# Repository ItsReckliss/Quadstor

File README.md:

# Quadstor

**Quadstor** is a modular, four-lane charger for **4S Li-ion, LiPo, and LiHV packs**, designed around the simple, balance-connector-only workflow of small FPV battery chargers such as Whoopstor and Toothstor. It is currently a **hardware/firmware design project**, not a validated or production-ready charger.

This README captures the intended product, established design decisions, explored alternatives, and unresolved engineering work so contributors and coding agents can pick up the project without reconstructing earlier discussions.

> **Status (30 September 2026):** The **power-source selection board schematic is drawn** (`Hardware/Power Board/Quadstor Power Board/`, 19 parts). Its parts are synced to a 45 × 45 mm, 2-layer PCB outline, but nothing is routed yet. A netlist review found **issues to fix before layout**, listed in [§3 Power board schematic](#power-board-schematic-as-drawn-2026-09-30). The project is a git repository published at [github.com/ItsReckliss/Quadstor](https://github.com/ItsReckliss/Quadstor). A **single-lane prototype** is the next hardware milestone before tiling the design four times. **BQ25792 (charge IC) is selected for the single-lane prototype**, with the **STM32G0B1 (microcontroller)** as the MCU. The BQ25713 (original charge controller) is kept as historical context and a fallback. No schematic, tested charging system, or firmware exists yet. Dated decisions are recorded in [§12 Decision log](#12-decision-log); datasheets are in `datasheets/`.

### Key parts at a glance

Parts are referred to by part number throughout; this table gives each one's job.

| Part | Purpose | Status |
|---|---|---|
| TI **BQ25792** | Charge IC: buck-boost battery charger with integrated FETs, one per lane | Selected for prototype |
| TI **BQ25713** | Charge controller: buck-boost charger needing external MOSFETs, one per lane | Superseded; fallback |
| ST **STM32G0B1** | Microcontroller (MCU): control, cell-tap ADC, UI, USB | Selected |
| TI **TCA9548A** | I²C multiplexer: gives each lane's charge IC its own bus (fixed-address workaround) | Selected |
| TI **TPS54160A** | Buck regulator: makes the logic supply (5 V/3.3 V) from the 24–25 V input | Selected |
| SSD1306-class OLED, 0.92" | Display (prototype): header row + one lane panel | Selected (exact module TBD) |
| Toshiba **TPHR8504PL** | Power MOSFET: BQ25713 switching stage (Q1–Q4) | BQ25713 design only |
| **AONR21307** | P-MOSFET: BATFET for the BQ25713 design | BQ25713 design only |
| **AO3401A** | P-MOSFET: bleed switch for cells 2–4 (high-side, cell-referenced) | Proposed (owner suggestion); datasheet in repo |
| **AO3400A** | N-MOSFET: bleed switch for cell 1 (ground-referenced) | Proposed |
| **2N7002** | Small N-MOSFET: level-shifting gate driver for each AO3401A | Proposed |
| BZT52C5V1 (5.1 V Zener) | Gate-source clamp protecting each AO3401A's ±12 V gate rating | Proposed |
| **NCE6003X** / **NTD5865NLT4G** | N-MOSFET: earlier bleed-switch candidates | Superseded by AO3401A/AO3400A proposal |
| TLV755P / AP2112K | LDO regulator: 5 V → clean 3.3 V | Proposed |
| 0603 10 kΩ NTC (B ≈ 3380–3435 K) | Temperature sensor on the charge IC's TS pin, next to the JST-XH | Decided (exact part TBD) |
| USBLC6-2SC6 | USB ESD protection on D+/D− | Proposed |
| TI **CD74HC4067SM96** | 16:1 analog multiplexer (SSOP-24, tape and reel): routes the 16 divided tap voltages to one MCU ADC pin | Selected (datasheet not yet in `datasheets/`) |
| **TLV9001** / **MCP6001** | Op-amp: unity-gain buffer between the analog mux and the ADC | Proposed |
| Tag-Connect TC2030 | Connector-less SWD programming/debug footprint | Proposed |
| Mean Well 24 V / 200 W | Internal power supply (model TBD) | Planned |
| **AOD409** (×3) | P-MOSFET, TO-252: power-board source switches (Q1 PSU path; Q2/Q3 back-to-back on the 6S path) | In power-board schematic |
| **2SA1213-Y** | PNP transistor, SC-62: power board, pulls the 6S FET gates off when the PSU is present (Q4) | In power-board schematic |
| **AO3400A** (power board) | N-MOSFET: power board PSU-present detector that drives Q4 (Q5) | In power-board schematic |
| **BZT52C12V** | 12 V Zener: power board gate-source clamp for the 6S FETs (U1) | In power-board schematic |
| **SMCJ30A-TR** (×2) | TVS diode, 30 V standoff: power board surge clamp on each input (D1 PSU, D2 6S) | In power-board schematic |
| Littelfuse **01550900M** (×2) | SMD fuse: power board, one per input (FH1 PSU, FH2 6S) | In power-board schematic; rating to confirm |

## 1. Product goals

- **Four independent 4S charging lanes**, each with a 5-pin JST-XH balance connector. Packs can be inserted/removed independently without disturbing other lanes.
- **Balance-connector-only charging:** the outer connector pins carry pack charging current; intermediate pins provide cell taps. No separate XT30/XT60 lead is required for the battery being charged.
- **User-selectable charging current:** 0.1–2.0 A per lane in 0.1 A steps. Earlier discussions refer both to a global current setting and per-lane adjustment; the UI behavior should be finalized in firmware requirements. The electrical architecture must support independently controlled lanes.
- **Global per-cell target voltage presets:** 3.80 V, 3.85 V, 4.20 V, and 4.35 V, corresponding to 15.20 V, 15.40 V, 16.80 V, and 17.40 V for a 4S pack. The 4.35 V setting is **LiHV only** and must not be applied to conventional 4.20 V/cell packs.
- **Passive cell balancing**, individual cell-voltage measurement, pack monitoring, and safe fault handling on every lane.
- Compact **OLED, two-button, and beeper** interface. The UI uses a **single OLED**. The prototype uses a small 0.92" OLED showing a **header** (input voltage, target voltage, set current) and **one lane panel**. The final version uses a larger single OLED with that lane panel **tiled four times** and a reorganized header (see §7).
- Operate from an **internal 24 V / 200 W Mean Well PSU** or an external **6S battery via XT60**, automatically preferring the PSU when available.
- Modular design: develop, assemble, and characterize one complete lane, then replicate it four times.

## 2. System overview

```text
                     Internal 24 V / 200 W PSU
                                |
External 6S pack -> XT60 -> input protection / source selection
                                |
                   Protected, selected VIN bus
                                |
                   Bulk decoupling near lanes
                                |
            +-------------------+-------------------+
            |                   |                   |
       Charger lane 1      Charger lane 2      ... lane 4
       4S JST-XH           4S JST-XH              4S JST-XH
       Cell taps           Cell taps              Cell taps
       4 bleed paths       4 bleed paths          4 bleed paths
            |                   |                   |
       I2C mux ch0         I2C mux ch1            I2C mux ch3
            +-------------------+-------------------+
                                |
                      TCA9548A I2C mux
                                |
        STM32G0B1: ADC (cell taps, VSENSE) / GPIO / USB
                                |
   Single OLED (header + lane panels) / 2 buttons / buzzer / LEDs / USB-C / SWD

Logic power: selected VIN -> TPS54160A buck -> 3.3 V (optionally 5 V -> LDO -> 3.3 V)
```

Each lane has its own charger power stage, pack sensing, balancing, and charging state. The **tiled hardware lane unit** is: BQ25792 charge IC + its inductor/capacitors, JST-XH, cell-tap sensing, four bleed paths, and NTC. The MCU, regulators, I²C mux, the single OLED, buttons, buzzer, USB-C, and SWD are **shared and are not tiled**. Tiling of the UI happens in **firmware**: one lane panel drawn four times on the one display (§7).

The BQ25792 charge IC has a fixed 7-bit I²C address (**0x6B**), so four of them cannot share one bus. A **TI TCA9548A** (8-channel I²C switch/multiplexer) gives each lane's charge IC its own downstream channel. The proposed channel map is ch0–ch3 for lanes 1–4 and ch4–ch7 spare. The single OLED (SSD1306-class, typically 0x3C) sits on the upstream bus, or on a spare channel if needed. If the final larger display uses SPI, it connects directly to the MCU instead. Tie A0–A2 low (address 0x70), connect RESET to an MCU GPIO to clear stuck buses, and fit pull-ups on the upstream bus and on each used downstream channel. The TCA9548A runs from 1.65–5.5 V at up to 400 kHz. This channel map is **proposed** until it is drawn in a schematic.

## 3. Power input and source selection

### Intended inputs

| Input | Nominal | Relevant range / notes |
|---|---:|---|
| Internal Mean Well PSU | 24 V, 200 W | Default source when present. Exact PSU model not yet recorded here. |
| External field battery | 6S Li-ion/LiPo via XT60 | Up to **25.2 V** for standard 4.20 V/cell 6S. Verify any LiHV input separately. |

The separately developed **power-selection board** accepts `VBAT`, `GND`, `GND`, and `VPSU`, and provides `VOUT`, `GND`, and `VSENSE`. `VSENSE` is intended to feed an MCU ADC through a resistor divider. The selected output feeds the charger board directly, with additional local bulk and high-frequency bypass capacitors at each charger IC.

**Confirmed by the owner (2026-09-29):** the existing power board already **handles source selection**, **electrically disconnects the XT60 input when the PSU is on**, and **blocks backfeed**. The charger lanes therefore do not need their own source selection or reverse-current blocking. ~~**Open item:** confirm whether the power board has a **TVS and/or soft-start**~~ **Answered by the schematic (2026-09-30):** both inputs have an SMCJ30A TVS diode, but it clamps far above the BQ25792 charge IC's 30 V absolute maximum, and there is no dedicated soft-start. See the review below. **Review note:** the drawn schematic does **not** block backfeed into the PSU (finding 2 below), so the owner's earlier confirmation needs to be rechecked.

Discussed input protection/components:

- 15 A fuse on the power input path (final placement/rating must be verified).
- Input TVS diode; proposed 100 µF bulk capacitor and 1 µF bypass capacitor.
- Back-to-back P-channel MOSFETs on the XT60 path for source isolation/reverse-current blocking.
- PSU-priority behavior: when PSU is present, block the external battery from supplying the bus; use the external battery when PSU is absent.
- `VSENSE` divider for firmware supply-voltage monitoring. Confirm which node it measures in the current schematic.

### Power board schematic (as drawn, 2026-09-30)

The KiCad 10 project is `Hardware/Power Board/Quadstor Power Board/`. Its parts were imported from LCSC with the EasyEDA importer into the project-local `EasyEDA.kicad_sym` / `EasyEDA.pretty` libraries. All 19 footprints are on a **45 × 45 mm, 2-layer** board outline (imported from DXF), with no tracks or copper zones yet.

| Ref | Part (LCSC) | Function |
|---|---|---|
| FH1, FH2 | Littelfuse 01550900M SMD fuse (C108518) | Input fuses: FH1 on `VPSU`, FH2 on `VBAT` (6S/XT60). Current rating not yet recorded. |
| D1, D2 | SMCJ30A-TR TVS diode (C1975473) | Surge clamps: D1 on `VPSU_Protected`, D2 on the fused 6S node |
| C1, C2 | 1 µF 100 V X7R 1206 (C91151) | C1 on `VPSU_Protected`, C2 on `VOUT` |
| Q1 | AOD409 P-MOSFET (C36220) | PSU path switch: source `VPSU_Protected`, drain `VOUT`. Gate is biased by the R1/R2 divider to Vgs ≈ −VPSU/2. |
| Q2, Q3 | AOD409 P-MOSFET (C36220) | 6S path, back-to-back with common sources. Q2 drain on the fused battery, Q3 drain on `VOUT`. |
| U1 | BZT52C12V 12 V Zener (C5182293) | Clamps the 6S FETs' gate (`VBAT_Gate`) to 12 V below their common source |
| Q4 | 2SA1213-Y PNP transistor (C396014) | When on, shorts `VBAT_Gate` to the common source, turning the 6S path off |
| Q5 | AO3400A N-MOSFET (C20917) | PSU-present detector: gate from the R6/R7 divider on `VPSU_Protected`; pulls Q4's base low through R4 |
| R1–R7 | Labeled "220k"; library part is RC0402FR-071KL (C106235) | Gate/bias dividers and pull-downs (see finding 3) |

**Intended operation:** with the PSU present, Q1 conducts and Q5 turns Q4 on, which holds the 6S FETs off, so the PSU has priority. With the PSU absent, Q5 and Q4 are off, and R3 pulls `VBAT_Gate` low (clamped by U1), turning Q2/Q3 on. Back-to-back Q2/Q3 block current in both directions when off.

Not yet in the schematic: input/output **connectors** (XT60, PSU input, output to the charger board; the nets are global labels only), the `VSENSE` divider, and the duplicate GND pins of the board interface.

**Review findings (Claude, from a netlist exported with kicad-cli on 2026-09-30; verify before layout):**

1. **Q2's gate is unconnected** (ERC net `unconnected-(Q2-G-Pad1)`). A third `VBAT_Gate` label exists but isn't attached. Without the gate, Q2 conducts only through its body diode or turns on unpredictably, and the 6S path can't block reverse current. Connect Q2's gate to `VBAT_Gate`.
2. **Q1 doesn't block backfeed into the PSU, and the PSU-detect can be fooled.** Q1's body diode conducts from drain to source (`VOUT` → `VPSU_Protected`). When running from the 6S pack with the PSU off, the pack feeds the PSU output through that diode. That also lifts `VPSU_Protected` to about VOUT − 0.7 V, which turns Q5 → Q4 on and shuts the 6S path off. The likely result is the battery path oscillating or failing to stay on. Fixing this needs a PSU-side switch that blocks in both directions (for example a back-to-back pair or an ideal-diode controller), or a PSU-present signal taken upstream of anything `VOUT` can back-drive.
3. **The resistor value doesn't match the part.** All seven resistors say **220k**, but their library part and LCSC number are **RC0402FR-071KL, which is 1 kΩ**. A BOM ordered by LCSC number would fit 1 kΩ. R1/R2 would then draw ~12 mA from 24 V and dissipate ~0.14 W each, above a 0402's typical 1/16 W rating. Pick a real 220 kΩ 0402 part and LCSC number.
4. **The TVS doesn't protect the BQ25792 charge IC's 30 V absolute maximum.** The SMCJ30A has a 30 V standoff, 33.3 V minimum breakdown, and ~48 V clamping at rated current (typical datasheet values). It catches large surges but lets `VOUT` exceed 30 V during a spike. This matches the reasoning behind "no per-lane TVS" in §4. Hot-plug ringing still needs scoping, and possibly a lower-voltage clamp or a soft-start/inrush limiter.
5. **Q5's gate margin is thin.** The R6/R7 divider gives VGS = VPSU/2, which is 12 V at 24 V. The AO3400A's gate rating is ±12 V (verify; datasheet not in repo), so a Mean Well PSU trimmed up, or a spike, overstresses it. Use a lower divider ratio (for example 220k over 100k) or a Zener clamp.

**Important:** Do not assume the power board provides a regulated 24 V output. The charger must tolerate the actual selected input voltage and transients. Absolute maximum is **not** a recommended continuous design target. Check the chosen IC's recommended operating range, transient headroom, TVS coordination, and hot-plug behavior before powering a prototype.

**BQ25792 (charge IC) input-voltage findings (datasheet SLUSDG1C, checked 2026-09-29):**

| Parameter | Value | Implication |
|---|---|---|
| VBUS/VAC absolute maximum | 30 V | A 25.2 V 6S pack will not damage the IC in steady state. Hot-plug ringing must stay below 30 V. That is the power board's job (TVS/soft-start still to be confirmed), because a per-lane TVS cannot do it (see §4). |
| VBUS recommended operating range | 3.6–24 V | The 24 V PSU is at the limit and acceptable. A full 6S pack (25.2 V) is ~1.2 V above the recommended range. |
| VAC OVP, highest setting (`VAC_OVP[1:0]=00`, default) | Rising: 25.2 / 26.0 / 26.8 V (min/typ/max). Falling: 24.4 / 25.2 / 26.0 V | A low-tolerance part could trip OVP on a fully charged 6S pack and stay off until the input falls below ~24.4 V. The expected result is a lane refusing to start or dropping out, not damage. |

**Decision (2026-09-29):** accept 6S direct input for the prototype and characterize it. Test with a freshly charged 6S pack, and scope VBUS during XT60 hot-plug. Firmware should detect and report the VAC OVP fault and retry. If lanes trip in practice, the options are a ~1 V drop on the 6S path (a diode, or preferably an ideal-diode controller for lower loss), a pre-regulator, or limiting the field input to 5S (21 V).

The proposed 200 W PSU is nominally sufficient for the planned four-lane output power under ideal conditions (4 × 17.4 V × 2 A = **139.2 W** at the maximum LiHV target), but input power, losses, balancing dissipation, wiring limits, and thermal derating must be measured.

## 4. Charger lane: baseline and alternative

### Original baseline: TI BQ25713 (charge controller)

The original architecture uses **one BQ25713 buck-boost charger IC per lane**, with an external switching power stage, an external BATFET, and MCU-controlled passive balancing. This is the historical baseline, not proof that the current schematic still uses it.

| Function | Discussed component | Quantity per lane | Status |
|---|---|---:|---|
| Buck-boost charger controller | TI **BQ25713** | 1 | Original baseline |
| Main switching MOSFETs Q1–Q4 | Toshiba **TPHR8504PL** N-MOSFET | 4 | Selected for original design |
| BATFET | **AONR21307** P-MOSFET | 1 | Selected/proposed; validate exact suffix and pinout |
| Passive balancing switches | **NCE6003X** N-MOSFET | 4 | Proposed; other candidates considered |
| Balance bleed resistors | **110 Ω, 1210, 0.5 W** | 4 | Proposed; requires thermal validation |
| Battery connector | **5-pin JST-XH** | 1 | Required interface |
| Cell sensing | MCU ADC with suitable front-end | 4 cell voltages derived from taps | Architecture only; protection/circuit not finalized |

The uploaded TPHR8504PL (power MOSFET) datasheet specifies a **40 V** drain-source rating and typical `RDS(on)` of **0.7 mΩ at VGS = 10 V** (0.85 mΩ max under its stated test conditions). It has substantial gate charge (103 nC typical at 10 V in the datasheet's stated test setup). Validate compatibility with the selected charger gate drivers, switching frequency, layout, and thermal design; low on-resistance alone does not establish suitability. The exact package variant/footprint must match the ordered device.

The **NTD5865NLT4G** was also investigated as a possible balancing MOSFET; it is **not** established as the final selection.

### Prototype selection: TI BQ25792 (charge IC)

**Decision (2026-09-29):** the single-lane prototype uses the **BQ25792**, a buck-boost charger with **integrated switching FETs** (datasheet in `datasheets/BQ25792_datasheet.pdf`, rev SLUSDG1C). It replaces the BQ25713's external Q1–Q4 stage, so the TPHR8504PL switches and the AONR21307 BATFET in the table above do **not** apply to this design. Never mix the two architectures' BOMs.

Datasheet facts relevant to Quadstor:

| Item | Datasheet value | Notes |
|---|---|---|
| Charge voltage (VREG) | 3.0–18.8 V, 10 mV steps | Covers all presets, including 17.40 V LiHV. |
| Charge voltage accuracy | +0.65% / −0.85% | At 17.40 V, +0.65% is +113 mV (≈4.378 V/cell average). Firmware must use per-cell measurements, not rely on VREG alone, to keep LiHV cells ≤4.35 V. |
| Charge current (ICHG) | 50 mA–5 A, 10 mA steps | Covers 0.1–2.0 A. Low-current accuracy is worse; for example, ±7.5% at 0.5 A. |
| Input current limit (IINDPM) | 0.1–3.3 A | Also limited by the ILIM_HIZ pin divider (V = 1 V + 0.8 × IINDPM). |
| Input voltage | See §3 | 24 V recommended max, 30 V abs max. |
| I²C | Fixed 7-bit address 0x6B | Requires the TCA9548A mux (§2). |
| Built-in ADC | VBUS, IBUS, VBAT, IBAT, TS, die temperature, and more | Lets the MCU read pack voltage/current and NTC temperature through I²C, which saves MCU ADC channels. |
| REGN | ~5 V LDO, 30 mA limit, needs 4.7 µF | For the IC's gate drive and TS bias only. **Do not** power the MCU/logic from it. |

Per-lane pin handling (proposed; verify against the datasheet when drawing the schematic):

- **PROG:** 17.4 kΩ selects 4S at 1.5 MHz (use a ~1 µH inductor); 27.0 kΩ selects 4S at 750 kHz (use a ~2.2 µH inductor). Choose based on efficiency and thermal testing.
- **VAC1/VAC2:** connect to VBUS, and tie **ACDRV1/ACDRV2** to GND. The power board does source selection, so the BQ25792's dual-input FETs are not fitted.
- **SDRV:** tie to GND or BAT because no ship FET is used.
- **CE (active low):** drive from an MCU GPIO with a **pull-up**, so charging is disabled while the MCU is in reset. It must never float.
- **INT and STAT:** open-drain outputs; use 10 kΩ pull-ups to 3.3 V and route to the MCU. INT is needed for fault handling. STAT is optional.
- **TS / temperature sensing (decided 2026-09-29):**
  - Fit **5.23 kΩ from REGN to TS** and **30.1 kΩ from TS to GND**, the TI typical-application divider in nearest E96 values. This gives the default window: charging suspends at ~0 °C and ~60 °C, with JEITA reductions near the edges.
  - Fit a **0603 10 kΩ NTC from TS to GND**. Use B ≈ 3380–3435 K; the datasheet recommends the 103AT-2 at B = 3435. 5% tolerance is acceptable.
  - Place the NTC **right next to the JST-XH connector**. It measures connector/board temperature, **not** the pack.
  - TS must **never float**. If temperature sensing is ever dropped, replace the NTC with a fixed 10 kΩ resistor.
- **D+/D−:** USB adapter detection is not used; follow the datasheet for unused handling.
- **OTG (reverse boost) mode (decided 2026-09-29):** the BQ25792 charge IC can boost the battery back out to VBUS. Firmware must **never enable OTG**, and must **read back that OTG is disabled** after configuring the IC, so a pack can never drive the input bus.
- **SYS:** the BQ25792 is a power-path (NVDC) charger, so SYS is powered from the pack when the input is removed. Fit only the required capacitors on SYS, with no other loads.
- **Input protection per lane (decided 2026-09-29):**
  - **No per-lane TVS.** The standoff would have to exceed 25.2 V (full 6S), and such a TVS clamps around 40 V, which is above the 30 V absolute maximum. Surge protection belongs on the power board (§3).
  - Add a **do-not-populate (DNP) footprint** for the datasheet's **input RC snubber (~2 Ω + 2.2 µF) on VBUS**. Fit it only if ringing shows up on the bench.
  - **Input capacitors:** VBUS gets 1× 0.1 µF + 2× 10 µF; PMID gets 1× 0.1 µF + 3× 10 µF. All are **50 V X7R**, derated for the 25.2 V input because ceramics lose capacitance under DC bias.
- **Other passives (datasheet values; ratings proposed):** SYS 1× 0.1 µF + 5× 10 µF (≥25 V, 35 V preferred at 17.4 V); BAT 2× 10 µF (≥25 V); BTST1 and BTST2 47 nF each; REGN 4.7 µF (10 V).

The BQ25713 charge-controller design remains a fallback if the BQ25792 charge IC fails characterization (input range, thermals, or accuracy). Switching back requires redesigning the power stage, not a part swap.

## 5. Battery connector and cell measurement

Each output is a **five-pin JST-XH connector for one 4S pack**. Number the contacts by **electrical function**, not assumed footprint orientation:

| Electrical node | Function |
|---|---|
| `B-` | Pack negative; charger negative connection |
| `B1` | Junction between cells 1 and 2 |
| `B2` | Junction between cells 2 and 3 |
| `B3` | Junction between cells 3 and 4 |
| `B+` | Pack positive; charger positive connection |

With taps referenced to `B-`, compute cell voltages as `Vcell1 = VB1`, `Vcell2 = VB2 - VB1`, `Vcell3 = VB3 - VB2`, and `Vcell4 = VB+ - VB3`.

**The MCU cannot directly connect upper-cell taps to ordinary 3.3 V ADC pins.** Provide properly rated dividers/buffers or a suitable multi-cell monitor, input protection, filtering, accurate reference/calibration, and safe handling of missing/intermittent contacts. Check voltage differences and resistor tolerances at every tap. Keep measurement input current and connector contact resistance in mind when charging through the same plug.

**Measurement architecture (decided 2026-09-29): an analog multiplexer feeding one MCU ADC pin.** The ADC is ground-referenced, so the system measures **tap voltages**, not cells directly. Per lane, the four taps B1, B2, B3, and B+ are measured, and cell voltages are computed by subtraction as above. Four lanes × 4 taps = **16 channels, one 16:1 analog mux**, with 4 MCU select GPIOs and 1 ADC input. `VSENSE` keeps its own ADC pin.

- **Pack voltage:** the B+ tap *is* the pack voltage, so no extra channel is needed. The BQ25792 charge IC also reports VBAT over I²C, which serves as an **independent cross-check**. A mismatch between the two ADCs should raise a fault.
- **Signal chain, per tap:** divider (0.1%) → series resistor + clamp → mux input. After the mux: a **unity-gain op-amp buffer** → MCU ADC.
  - Divide **before** the mux, because common muxes only pass signals within their 3.3–5 V supply.
  - The buffer isolates the divider's high source impedance and the mux on-resistance from the ADC sampling capacitor.
- **Settling:** allow settling time after each channel switch (tens of µs; confirm on the bench). Pause balancing on a lane while reading its taps.
- **Unpowered safety:** a pack can be connected while the board is unpowered, so the series resistors must limit injection current into the unpowered mux.
- **Standby drain:** the dividers drain packs left connected (e.g. ~170 µA at 100 kΩ total). Use high-value dividers (then the buffer is mandatory) or switch the dividers off when idle.
- **Accuracy:** all taps share one mux, buffer, and ADC path, so the offset is common. Differencing still amplifies divider error: 0.1% at ~13–17 V is roughly ±13–17 mV per tap. Plan two-point calibration per channel.
- **Candidate parts (proposed):**
  - **Selected (2026-09-29): TI CD74HC4067SM96** (16:1 analog multiplexer, SSOP-24, 0.65 mm pitch; the SOIC-24 variant CD74HC4067M96 is electrically identical).
    - Power it from 3.3 V (same as the ADC). Signals must stay within GND to VCC.
    - Tie E (active-low enable) to GND or to a GPIO.
    - On-resistance is ~70 Ω typical at 4.5 V and higher at 3.3 V. The buffer makes this irrelevant.
    - **Off-leakage × divider Thevenin resistance is an error source:** e.g. 1 µA × 25 kΩ = 25 mV at the ADC, ≈175 mV referred to a 17 V tap. Check the datasheet's leakage over temperature when choosing divider values.
  - Alternative: **ADG706** (Analog Devices, 16:1 analog multiplexer, ~2.5 Ω, lower leakage).
  - **TLV9001** or **MCP6001** (rail-to-rail op-amp) as the buffer.
- **Single-lane prototype:** fit the full 16:1 mux even though only 4 channels are used, to validate the four-lane measurement chain.

Tap front-end details still to design: divider values scaled to the ADC reference (for example B+ at 17.4 V max scaled to ≤2.5 V), clamp type, filter capacitor, and open/missing-tap detection (such as a weak bias that drives an unconnected tap to an implausible reading). A dedicated multi-cell monitor IC per lane remains an alternative if accuracy proves insufficient.

## 6. Passive balancing

The proposed architecture has **four independent bleed paths per lane**, one across each cell, each controlled by an external MOSFET under MCU supervision. The original candidate network is **110 Ω / 0.5 W (1210)** per cell, switched using NCE6003X MOSFETs (or a validated equivalent).

Approximate ideal resistor dissipation and bleed current:

| Cell voltage | Current through 110 Ω | Resistor dissipation |
|---:|---:|---:|
| 3.80 V | 34.5 mA | 0.131 W |
| 4.20 V | 38.2 mA | 0.160 W |
| 4.35 V | 39.5 mA | 0.172 W |

These values are estimates before switch losses and component tolerances. Verify each bleed path's **gate-drive voltage relative to its cell**, especially upper cells; do not connect high-side cell-referenced gates directly to ground-referenced MCU GPIOs. Upper-cell switches sit up to ~13 V above ground, so they need level shifting.

**Proposed bleed-switch circuit (2026-09-29).** The owner suggested the AO3401A (P-MOSFET). Its figures below were checked against `datasheets/AO3401A.pdf` (AOS Rev 3.1, Dec 2023) on 2026-09-30.

- **Cells 2–4 (upper cells):**
  - The **AO3401A** source goes to the cell's top node (B1/B2/B3/B+), and its drain goes through the 110 Ω bleed resistor to the cell's bottom node.
  - A 100 kΩ gate-to-source pull-up holds it off.
  - A **2N7002** N-MOSFET, gate driven by an MCU GPIO with a 100 kΩ pull-down, pulls the gate toward GND through ~47 kΩ.
  - A **5.1 V Zener** from gate to source clamps V_GS to about −5 V.
  - Why this is needed: the AO3401A's V_GS limit is **±12 V**, so the gate must never be pulled straight to GND. On the top cell that would apply ~−17 V.
  - AO3401A (datasheet): −30 V V_DS, ±12 V V_GS, 47 mΩ typical / 60 mΩ max at V_GS = −4.5 V, V_GS(th) −0.5 / −0.9 / −1.3 V (min/typ/max), SOT-23. At 40 mA the conduction loss is negligible.
  - Off-state leakage I_DSS is at most 1 µA at 25 °C (5 µA at 55 °C) per switch. This is small next to the tap-divider drain (§5) but adds to it on a stored, plugged-in pack.
- **Cell 1 (bottom cell):** B− is GND, so an **AO3400A** N-MOSFET is driven directly from a GPIO, with a 100 kΩ pull-down.
- **Why not N-channel on the upper cells:**
  - An upper-cell N-FET's source sits at that cell's bottom node (up to ~13 V). Its gate would need to be driven to about the cell's top node, which requires a high-side (P-type) switch plus its own driver. That is two driver transistors per upper cell.
  - A P-FET with its source on the cell's top node turns on by pulling its gate *down*, which one ground-referenced 2N7002 can do.
  - Totals per lane: 7 transistors with the proposed P-channel scheme, versus 10 for all N-channel.
- **Alternative:** one PhotoMOS solid-state relay per cell (for example the Panasonic AQY21x class). It needs no level shifting and fails off, but costs more (~$1–2 each) and is larger.
- **Fail-safe:** with the GPIO low, floating, or in reset, every bleed switch is off.
- **Per lane:** 3× AO3401A, 1× AO3400A, 3× 2N7002, 3× 5.1 V Zener.
- **To validate:** off-state leakage (a continuous drain on a stored, plugged-in pack), and tap-reading error while bleeding. Firmware should pause bleeding during cell measurements.

Four lanes × 4 bleed paths = **16 MCU GPIOs**, and every gate must have a pull-down or equivalent so all bleeders are **off during reset**. Ensure balancing cannot remain latched on after MCU reset and that balancing and charging decisions account for measured cell voltages, thermal limits, and the relatively low ~40 mA bleed rate compared with up to 2 A charging current.

## 7. MCU, firmware, and controls

### MCU: STM32G0B1 (microcontroller)

**Decision (2026-09-29):** STM32G0B1 (Cortex-M0+, 64 MHz; datasheet in `datasheets/STM32G0B1_datasheet.pdf`). It was chosen for its 16-channel 12-bit ADC, crystal-less USB 2.0 FS device, and ROM bootloader.

- **Package (proposed): LQFP64 (STM32G0B1RET6).** With the analog mux, the four-lane pin budget is 1 ADC for taps + 4 mux selects + 1 ADC for `VSENSE`, 16 balance GPIOs, 4 × CE + 4 × INT (optionally 4 × STAT), I²C, TCA9548A (I²C mux) RESET, USB D+/D−, SWD, 2 buttons, buzzer PWM, status LEDs, and possibly SPI for the final display. That is too tight for a 48-pin package. Use the same part on the single-lane prototype so firmware carries over.
- **Support circuitry:** 100 nF at every VDD pin plus 4.7 µF bulk; VDDA filtered with a ferrite bead, 1 µF, and 100 nF; 100 nF on NRST. Use VREF+ with the internal VREFBUF (2.048/2.5 V) or an external reference for ADC accuracy. No HSE crystal is needed, because USB uses HSI48 with clock recovery.
- **Safe defaults:** all charge-enable and balance outputs must default to off through external pulls, independent of firmware (see §6 and §8).

### Logic power

**Decision (2026-09-29):** a **TI TPS54160A** (3.5–60 V in, 1.5 A, non-synchronous buck; datasheet in `datasheets/tps54160a.pdf`) generates the logic supply from the selected VIN. An LDO from ~25 V was rejected because it would dissipate ~1 W at only 50 mA.

Design notes:

- **Switching frequency:** the minimum on-time is 130 ns typical. For 3.3 V output from up to 30 V in, f_SW(max) ≈ (3.3 + 0.5) / (30 V × 130 ns) ≈ 950 kHz. Use **~500–700 kHz**.
- **Catch diode:** requires an external Schottky from PH to GND, rated ~60 V / 1 A.
- **EN UVLO:** use a divider on EN so the regulator does not start until the input reaches roughly 8 V or more.
- **Components:** use 50 V-rated input capacitors, and compute compensation and the inductor with TI WEBBENCH.
- **Load:** the logic load is expected to be ≤ ~150 mA (MCU, OLEDs, mux, sensing), far below the 1.5 A rating.
- **Proposed topology:** buck to **5 V**, then a small low-noise LDO regulator (for example TLV755P or AP2112K) to 3.3 V. This gives a quieter ADC supply, a 5 V rail for the buzzer, and allows USB VBUS to be diode-ORed into the 5 V rail (see below). Buck directly to 3.3 V is acceptable if that is not wanted.

### Programming, USB, and diagnostics

**Decision (2026-09-29):** a **USB-C port on the controller/lane board** is for **flashing (USB DFU) and diagnostics (USB CDC virtual COM port)**. It is **not** a charging power input, since USB cannot supply the charging power, and it does not belong on the power board.

- **USB-C device wiring:** 5.1 kΩ Rd from each CC pin to GND; USB ESD protection (for example USBLC6-2SC6) on D+/D−; D+/D− to PA12/PA11.
- **Optional:** USB VBUS → Schottky → 5 V logic rail. This lets the MCU, OLEDs, buttons, buzzer, and USB be brought up with only a USB cable while the chargers stay unpowered, because their VBUS comes only from the power board. Ensure VBUS is never back-fed.
- **DFU entry:** a blank device boots the ROM bootloader automatically. Once flash is programmed, DFU entry needs either a firmware "jump to bootloader" command or the BOOT0 pin. On STM32G0 the BOOT0 function shares PA14 with SWCLK and is governed by option bytes (`nBOOT_SEL`/`nBOOT0`). Verify in RM0444 and AN2606 before relying on a BOOT button.
- **Buttons:** a **RESET button** (NRST to GND) and a **BOOT button** (PA14 to 3.3 V with a 10 kΩ pull-down) are planned for the prototype.
- **SWD is kept.** It is needed for debugging (breakpoints) and for recovery when bad firmware breaks USB. Earlier plans called for a JST-XH SWD header; the updated plan is a **Tag-Connect TC2030 footprint or bare pads** (3V3, SWDIO, SWCLK, NRST, GND) on both prototype and production, with no connector BOM cost. An optional UART TX test pad is useful for early logging.

### Intended UI

**Decision (2026-09-29):** the UI parts (OLED, buttons, buzzer, status LEDs) go on the single-lane prototype board so they can be verified before the four-lane build.

- **Single OLED (decided 2026-09-29):** there is exactly **one** display, never one per lane.
  - **Prototype:** a small **0.92" OLED**. Most modules this size are 128×32 SSD1306 I²C (display controller); confirm the actual resolution and controller of the purchased module. Connect it with a 4-pin header (VCC, GND, SCL, SDA) rather than a bare glass panel with FPC and charge-pump capacitors.
  - **Final:** a **larger single OLED** (part TBD). The prototype's lane panel is **tiled four times** on it, and the header is added or reorganized to fit.
- **Header row:** shows **input voltage, target voltage, and set current**, and may also show the power source and mute state if space allows. For example, `24.1V 4.20V 2.0A` is 16 characters, about 96 px in a 6 px-wide font, so it fits in 128 px.
- **Lane panel (the tiled unit in firmware):** connection/charging state, pack and cell voltages, charge current, and fault or completion. Implement it as a **self-contained, fixed-size render component** that takes a lane index and an (x, y) origin, so the final display simply draws it four times.
- **Proposed layout (not decided):**
  - On a 128×32 prototype display, use an **8 px header row + a 128×24 lane panel**.
  - A final **256×64** display (for example the SSD1322 class, commonly 2.8"–3.12") would fit the 8 px header plus four 128×24 panels in a 2×2 grid (8 + 48 = 56 px ≤ 64 px) without redesigning the panel.
  - Larger 256×64 panels are often SPI and 4-bit grayscale, which needs a different driver than the SSD1306. Keep SPI-capable MCU pins available.
- **Refresh budget:** a full 128×32 SSD1306 frame is 512 bytes, ~13 ms at 400 kHz I²C. A 256×64 grayscale frame is 8 KB, which is why the final display should use SPI and/or partial updates.
- **Two physical buttons:** tactile switches to GND with pull-ups and an optional 100 nF debounce, on interrupt-capable pins. One combines **Start/Stop + Current** and the other **Mute + Voltage**, using click/hold interactions. Final click/hold mappings, per-lane selection, and display layout need a firmware specification.
- **Beeper:** a passive magnetic buzzer driven from a timer PWM output (allowing distinct tones) through an N-MOSFET/NPN from the 5 V rail, with a flyback diode. It gives status, completion, and error notifications with mute support.
- **Status LEDs:** one power LED on 3.3 V plus one or two GPIO LEDs (~1 kΩ) for heartbeat and fault, useful before the OLED works.

The recorded product goals include a global current setting **and** a requirement to independently adjust each lane's current; this needs a deliberate UI decision rather than an assumed implementation. The planned header display shows one "set current," which implies a **global setpoint by default**. Whether per-lane overrides exist, and how they are shown in the lane panels, is still open. At minimum, the charger hardware and firmware should independently control and stop each lane.

### Suggested firmware modules (proposed, not existing code)

```text
firmware/
  board/             # GPIO, ADC, I2C, timer, and peripheral definitions
  power/             # VIN measurement and source status
  charger/           # Charger-IC abstraction, one instance per lane
  sensing/           # Tap acquisition, calibration, cell-voltage calculation
  balancing/         # Per-cell bleed control and safeguards
  safety/            # Fault detection, limits, watchdog, safe shutdown
  ui/                # OLED pages, button events, buzzer
  app/               # Global settings and four independent lane state machines
```

A sensible lane state machine to implement and validate is `DISCONNECTED -> DETECTED -> VALIDATING -> CHARGING -> COMPLETE`, with independently reachable `FAULT` and `STOPPED` states. This is a **proposed software design**, not an already implemented protocol.

Firmware must not enable charge solely because pack voltage appears plausible. Validate all cell taps and their ordering, detect absent/open wires and impossible voltages, configure and read back charger limits, check charger faults, and independently stop a lane when unsafe. Implement watchdog and brownout behavior that defaults all charge and balance switches to a safe state. Never enable the BQ25792 charge IC's OTG (reverse boost) mode, and read back that it is disabled after every configuration (§4).

## 8. Safety-critical design and test requirements

**Quadstor handles lithium batteries. This README is design context, not an assurance that the proposed circuitry is safe. Do not attach valuable packs or leave prototypes unattended before electrical and fault testing.**

Required engineering validation includes:

1. **Input:** PSU/6S switchover, reverse polarity, hot-plug, overvoltage/transients, reverse-current blocking, fuse and TVS selection, and 6S maximum voltage with design margin.
2. **Charging:** chosen IC's actual operating limits, current/voltage programming, charge termination, precharge/recovery policy, and pack temperature handling where sensing is available.
3. **Cell taps:** reversed connector, open/misaligned/intermittent taps, contact heating at up to 2 A, ADC protection, voltage accuracy, and independent overvoltage detection/shutdown strategy.
4. **Balancing:** upper-cell switch drive, leakage when off, stuck-on MOSFET, resistor temperature, ADC readings with bleeders active, and behavior during reset/power loss.
5. **Thermal/power:** inductor and MOSFET losses, IC temperature, copper/connector ratings, simultaneous four-lane load, and enclosure ventilation.
6. **Firmware:** startup with a pack already inserted, insertion/removal during charge, fault latching/recovery, brownouts, watchdog, and independent lane operation.

Prefer current-limited bench supplies and a battery simulator / resistive test fixtures for initial bring-up. Do not infer cell health from pack voltage alone.

## 9. Development plan and current open decisions

| Stage | Deliverable | State |
|---|---|---|
| Power board | PSU-priority selection, XT60 backup, protected `VOUT`, `VSENSE` | Schematic drawn (2026-09-30); 5 review findings to fix (§3); connectors and `VSENSE` not yet drawn; PCB outline only, unrouted |
| Single-lane schematic | BQ25792 lane (JST-XH, sensing, four bleed paths, NTC) plus STM32G0B1 MCU, TCA9548A I²C mux, TPS54160A buck regulator for the logic supply, 0.92" OLED, USB-C, SWD pads, buttons, buzzer, LEDs | Next milestone; ICs selected, schematic not started |
| Single-lane PCB | Assemble and test at low current | Planned |
| Firmware bring-up | Read charger registers, measure cell taps, control charge and bleed paths | Planned |
| Safety characterization | Voltage/current calibration, faults, switchover, thermal testing | Required before scaling |
| Four-lane board | Replicate proven lane, shared source bus and controller | Planned |
| Integrated UI/enclosure | Four independent statuses and user controls | Planned |

**Decisions that must be resolved before another agent finalizes a PCB:**

- ~~**BQ25713 vs BQ25792**~~: resolved as the BQ25792 charge IC for the prototype (§4). Still open is whether full-6S input (25.2 V vs the 24 V recommended max and ~25.2 V minimum OVP trip) works in practice (§3).
- **LiHV accuracy:** the BQ25792 charge IC's VREG (charge-voltage) tolerance (+0.65%) can exceed 4.35 V/cell at 17.40 V. Decide the firmware strategy, such as setting VREG slightly low or terminating on per-cell readings.
- **Current-setting semantics:** a global setpoint is shown in the header; are per-lane overrides needed, and how are lanes selected with two buttons?
- **Sensing and balancing:** ~~MCU choice~~ (STM32G0B1 microcontroller, LQFP64 proposed); ADC reference choice, tap front-end component values, upper-cell balance gate drivers, and whether a dedicated battery-monitor IC is needed.
- **Logic supply:** buck directly to 3.3 V, or buck to 5 V plus LDO (proposed); USB VBUS diode-OR yes or no.
- **Display:** the final larger single OLED (size, resolution, controller, I²C vs SPI); the lane panel pixel size (proposed 128×24) so four tiles plus the header fit; the I²C mux channel map (proposed ch0–3 lanes).
- **Protection:** battery temperature sensing, independent overvoltage cutoff, connector current rating, thermal sensors, fault thresholds, and charge enable interlocks.
- **Power board:** the schematic and part numbers are now in the repo (§3). Before layout, fix the unconnected Q2 gate, the backfeed path through Q1 / false PSU detection, the 220k vs 1 kΩ resistor mismatch, and Q5's gate margin. Also decide whether the SMCJ30A TVS diodes are enough given they clamp above 30 V, add the connectors and the `VSENSE` divider, and record the fuse rating. Test results are still needed.
- **Physical design:** OLED and connector part numbers, board dimensions, cooling/enclosure, PCB stackup, exact BOM, and firmware repository/toolchain.

## 10. Handoff instructions for contributors and agents

1. **Read this README and inspect the latest schematics, BOM, and PCB files.** Conversation-era part choices are historical context; the checked-in schematic is authoritative for what is actually built.
2. **Separate requirements from proposals.** Four 4S lanes, JST-XH-only pack connections, target-voltage presets, dual input with PSU priority, OLED/two-button UI, and passive balancing are project goals. Charger IC, MCU, sensing topology, and detailed firmware architecture may change.
3. **Do not assume tested functionality.** Mark every claim as proposed, schematic-complete, assembled, bench-tested, or battery-tested, with evidence and revision.
4. **When modifying hardware, update the README/BOM and record why** (input voltage margin, efficiency, thermal performance, supply availability, safety, etc.). Never swap the BQ25713 and BQ25792 charge ICs without redesigning the corresponding power stage.
5. **Before implementing charge control, confirm** the exact IC datasheet/register map, valid pack-voltage range, hardware safety defaults, cell-measurement calibration, and independent fault handling.
6. **Develop one lane first**, validate it under simulated and controlled loads, then replicate the proven circuitry to four lanes.
7. **Record every new determination in §12 Decision log** with its date and reasoning, and update the affected sections. Mark superseded options instead of deleting them.

### Suggested repository structure

```text
Quadstor/
├── README.md
├── docs/
│   ├── architecture.md
│   ├── decisions.md        # Dated design decisions and superseded options
│   ├── safety-test-plan.md
│   └── bringup-log.md      # Revision-specific measurements and failures
├── hardware/
│   ├── power-selection/
│   ├── single-lane/
│   └── four-lane/
├── firmware/
├── datasheets/             # Link to vendor docs or include where permitted
└── images/
```

The structure above is a **suggestion**. As of 2026-09-30, the repository contains:

- `README.md` and a `.gitignore`. The `.gitignore` excludes KiCad lock files (`~*.lck`), `*-backups/`, `fp-info-cache`, `*.kicad_prl`, and `_autosave-*`.
- `datasheets/` (see §11).
- `Hardware/Power Board/Quadstor Power Board/`: the KiCad 10 power board project (schematic drawn, PCB outline placed), plus its project-local `EasyEDA.kicad_sym`, `EasyEDA.pretty`, and `EasyEDA.3dshapes` libraries.
- `Hardware/Charge Board/` and `Hardware/Single Module (TEST)/` also exist locally but are empty. Git doesn't track empty folders, so they don't appear on GitHub yet.

The repository is published at [github.com/ItsReckliss/Quadstor](https://github.com/ItsReckliss/Quadstor) (`origin`, branch `main`).

**KiCad library gotcha:** the EasyEDA/LCSC importer once wrote the project's `fp-lib-table` with a `(sym_lib_table` header instead of `(fp_lib_table`. KiCad then ignores the footprint library, and "Update PCB from Schematic" reports every `EasyEDA:...` footprint as "not found." To fix it, change the first line to `(fp_lib_table` with the project closed, then reopen it. Also check that `sym-lib-table` starts with `(sym_lib_table`.

## 11. References

Datasheets in `datasheets/`:

- **`BQ25792_datasheet.pdf`:** TI BQ25792 charge IC (SLUSDG1C, Aug 2022), selected for the prototype.
- **`STM32G0B1_datasheet.pdf`:** ST STM32G0B1 microcontroller, the selected MCU. The reference manual RM0444 and bootloader note AN2606 are also needed and not yet in the repo.
- **`tca9548a.pdf`:** TI TCA9548A 8-channel I²C switch/multiplexer.
- **`tps54160a.pdf`:** TI TPS54160A 60 V buck regulator (SLVSB56C), for the logic supply.
- **`AO3401A.pdf`:** AOS AO3401A 30 V P-MOSFET (Rev 3.1, Dec 2023), the proposed bleed switch for cells 2–4.

Datasheets for the power board parts (AOD409, 2SA1213-Y, AO3400A, BZT52C12V, SMCJ30A, 01550900M) and for the CD74HC4067SM96 analog mux aren't in the repo yet.

Other:

- **TI BQ25713 (charge controller):** original external-MOSFET buck-boost charger baseline and current fallback; consult the current TI datasheet and reference design.
- **Toshiba TPHR8504PL (power MOSFET for the BQ25713 stage):** supplied project datasheet, including ratings, gate charge, electrical characteristics, and package drawings. Verify the actual revision and package against purchased parts.
- **AONR21307 (BATFET), NCE6003X and NTD5865NLT4G (balancing MOSFETs):** candidate/selected devices from earlier design discussions; retrieve authoritative datasheets before layout.

## 12. Decision log

Newest first. Status is **Decided** (the owner chose it), **Proposed** (recommended, not yet confirmed), or **Superseded**.

| Date | Decision | Status | Reasoning / notes |
|---|---|---|---|
| 2026-09-30 | Power board schematic: AOD409 P-MOSFET PSU switch (Q1); back-to-back AOD409 6S path (Q2/Q3) with BZT52C12V gate clamp; 2SA1213-Y PNP + AO3400A N-MOSFET PSU-present override; SMCJ30A TVS and 01550900M fuse on each input; 45 × 45 mm 2-layer outline | Decided (owner's schematic); fixes pending | Implements PSU priority with the 6S path off when the PSU is present. The netlist review in §3 found an unconnected Q2 gate, backfeed through Q1's body diode that can also falsely trigger PSU detection, 220k-labeled resistors whose part number is 1 kΩ, a TVS that clamps above 30 V, and thin Q5 gate margin. |
| 2026-09-30 | AO3401A bleed-switch figures verified against the datasheet | Verified | ±12 V V_GS confirmed, so the 5.1 V Zener gate clamp remains necessary; 60 mΩ max at −4.5 V; I_DSS ≤ 1 µA at 25 °C. |
| 2026-09-30 | Project tracked in git and published to github.com/ItsReckliss/Quadstor, with a KiCad `.gitignore` | Decided | Lock files, backups, autosaves, and per-user `.kicad_prl` view settings are excluded. |
| 2026-09-29 | TS: 5.23 kΩ REGN→TS, 30.1 kΩ TS→GND, 0603 10 kΩ NTC (B ≈ 3380–3435 K, 5%) next to the JST-XH. Fixed 10 kΩ if sensing is ever dropped. | Decided | TI typical-application divider (E96 values) keeps the datasheet's 0–60 °C / JEITA thresholds. Measures connector/board temperature, not the pack. |
| 2026-09-29 | Lane input protection: no per-lane TVS; DNP footprint for the ~2 Ω + 2.2 µF VBUS snubber; VBUS 0.1 µF + 2× 10 µF and PMID 0.1 µF + 3× 10 µF, all 50 V X7R | Decided | A TVS with >25.2 V standoff clamps ~40 V, above the 30 V abs max. The power board already does source selection, XT60 disconnect with the PSU on, and backfeed blocking. Its TVS/soft-start is still an open question. |
| 2026-09-29 | Firmware must never enable BQ25792 OTG (reverse boost) mode, and must read back that it is off after configuration | Decided | Prevents a pack from driving the input bus. |
| 2026-09-29 | **Single OLED.** The prototype uses a 0.92" OLED with a header (input V, target V, set current) and one lane panel. The final version uses a larger single OLED with the lane panel tiled 4× and a reorganized header. | Decided (final display part and panel pixel sizes proposed) | Tiling is done in firmware, not hardware. Lane-panel code must be a reusable fixed-size component. |
| 2026-09-29 | One OLED per lane plus a separate header display | Superseded | Logged in error from a misread of the owner's intent; replaced by the single-OLED decision above. |
| 2026-09-29 | OLED, buttons, buzzer, and status LEDs on the single-lane prototype | Decided | Verify the UI hardware before the four-lane build. |
| 2026-09-29 | SWD via Tag-Connect TC2030 footprint or bare pads instead of a JST-XH header | Proposed | USB DFU covers routine flashing; SWD is still needed for debugging and recovery. No connector BOM cost. |
| 2026-09-29 | USB-C on the controller/lane board for DFU flashing and CDC diagnostics, not power | Decided | USB can't deliver charging power; it is a data/service port, so it doesn't belong on the power board. |
| 2026-09-29 | RESET and BOOT buttons on the prototype | Proposed | BOOT0 needs the option-byte change on STM32G0 (verify in RM0444). |
| 2026-09-29 | TPS54160A buck regulator for the logic supply | Decided | 60 V input gives wide margin over the 30 V worst case. An LDO from 25 V would dissipate ~1 W. Run at ~500–700 kHz because of the 130 ns minimum on-time. |
| 2026-09-29 | Buck to 5 V, then LDO to 3.3 V; optional USB VBUS diode-OR into 5 V | Proposed | Quieter ADC rail, a 5 V buzzer rail, and USB-only bring-up of logic/UI. |
| 2026-09-29 | STM32G0B1 microcontroller, LQFP64 package | MCU decided; package proposed | 12-bit ADC (taps now read through an external analog mux, so few channels are needed), crystal-less USB with ROM DFU; the pin budget needs 64 pins. |
| 2026-09-29 | TCA9548A I²C mux; ch0–3 lanes, ch4–7 spare | Part decided; map proposed | The BQ25792 charge IC's address is fixed at 0x6B. |
| 2026-09-29 | Accept direct 6S input for the prototype and characterize OVP/hot-plug behavior | Decided | The 30 V abs max is not exceeded, but 25.2 V is above the 24 V recommended max and at the minimum OVP trip. Fallbacks are listed in §3. |
| 2026-09-29 | BQ25792 charge IC for the single-lane prototype | Decided | Integrated FETs reduce BOM and layout complexity; VREG up to 18.8 V covers 17.40 V LiHV. |
| 2026-09-29 | Cell measurement via one 16:1 analog mux (16 divided taps) + op-amp buffer into one MCU ADC pin; pack voltage from the B+ tap, cross-checked with the BQ25792 charge IC's VBAT reading | Decided (owner); mux = CD74HC4067SM96 (owner); op-amp proposed | Uses 1 ADC + 4 select pins instead of 13 ADC channels. Taps, not cells, are measured, and cells are computed by subtraction. Supersedes the 13-channel direct-ADC plan. |
| 2026-09-29 | Bleed switches: AO3401A P-MOSFET (cells 2–4) with 2N7002 level-shift + 5.1 V Zener gate clamp; AO3400A N-MOSFET (cell 1) | Proposed (owner suggested AO3401A; circuit is Claude's proposal) | P-channel with source on the cell's top node needs no floating gate supply. The Zener protects the ±12 V gate rating. Fails safe (off) at reset. Supersedes the NCE6003X/NTD5865NLT4G candidates. |
| earlier | BQ25713 charge controller + TPHR8504PL power MOSFETs ×4 + AONR21307 BATFET | Superseded (fallback) | Original baseline; see §4. |

---

**Project intent:** a convenient, independently controlled, four-port 4S balance-plug charger that works on the bench from its internal PSU and in the field from a 6S pack. The immediate priority is a **safe, instrumented, single-lane proof of concept**, not prematurely committing to a four-lane production PCB.

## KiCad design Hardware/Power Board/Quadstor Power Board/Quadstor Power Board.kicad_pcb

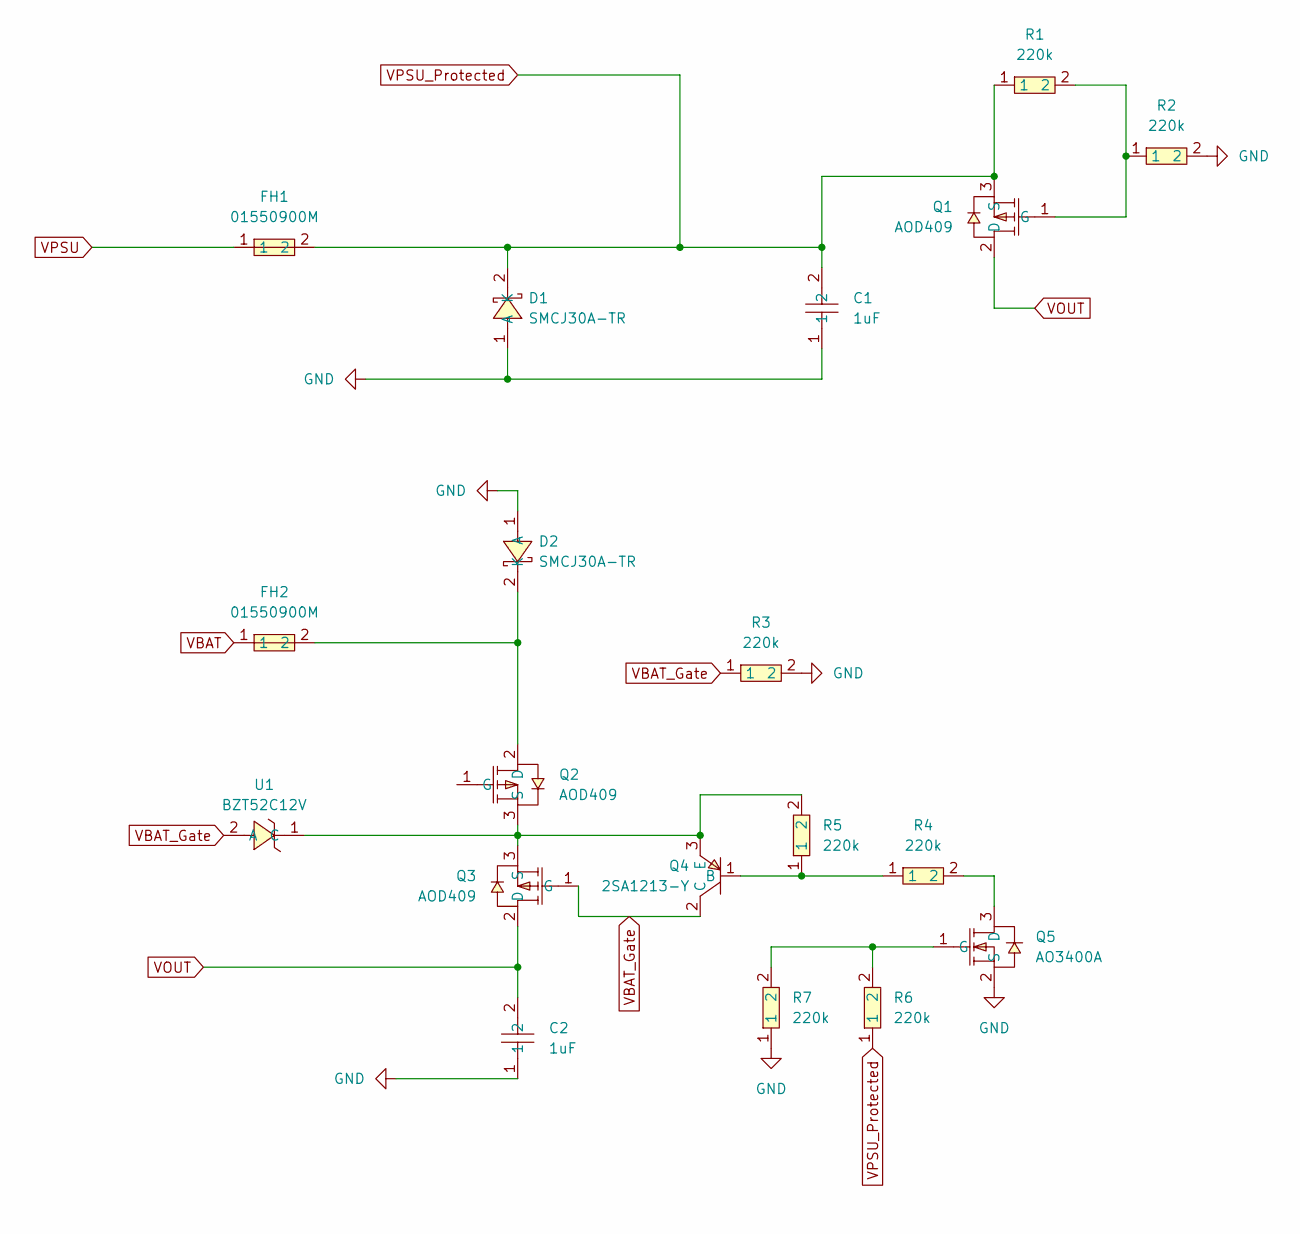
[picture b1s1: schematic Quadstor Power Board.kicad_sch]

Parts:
C1, C2: 1uF; C1206; MPN 1206B105K101NT; LCSC Part C91151
D1, D2: SMCJ30A-TR; SMC_L6.9-W5.9-LS7.9-R-RD; MPN SMCJ30A-TR; LCSC Part C1975473
FH1, FH2: 01550900M; FUSE-SMD_L9.8-W5.0_01550900M; MPN 01550900M; LCSC Part C108518
Q1, Q2, Q3: AOD409; TO-252-2_L6.6-W6.1-P4.57-LS9.9-TL-CW; MPN AOD409; LCSC Part C36220
Q4: 2SA1213-Y; SC-62_L4.6-W2.5-P1.50-LS4.2-BR; MPN 2SA1213-Y(TE12L,ZC; LCSC Part C396014
Q5: AO3400A; SOT-23-3_L2.9-W1.3-P1.90-LS2.4-BR; MPN AO3400A; LCSC Part C20917
R1, R2, R3, R4, R5, R6, R7: 220k; R0402; MPN RC0402FR-071KL; LCSC Part C106235
U1: BZT52C12V; SOD-123_L2.7-W1.6-LS3.7-RD-1; MPN BZT52C12V; LCSC Part C5182293

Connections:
GND: C1.1, C2.1, D1.1 (A), D2.1 (A), Q5.2 (S), R2.2, R3.2, R7.1
unnamed: D2.2 (K), FH2.2, Q2.2 (D)
unnamed: Q1.1 (G), R1.2, R2.1
unnamed: Q2.3 (S), Q3.3 (S), Q4.3 (E), R5.2, U1.1 (C)
unnamed: Q4.1 (B), R4.1, R5.1
unnamed: Q5.3 (D), R4.2
unnamed: Q5.1 (G), R6.2, R7.2
VBAT: FH2.1
VBAT_Gate: Q3.1 (G), Q4.2 (C), R3.1, U1.2 (A)
VOUT: C2.2, Q1.2 (D), Q3.2 (D)
VPSU: FH1.1
VPSU_Protected: C1.2, D1.2 (K), FH1.2, Q1.3 (S), R1.1, R6.1

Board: 2 copper layers, 19 parts (0 on the bottom side), 10 nets, no tracks yet.
